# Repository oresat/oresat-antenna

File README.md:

# oresat-antenna
This is a place for RF details of the antennas used on the OreSat CubeSat

On the OreSat structure there are antennas placed on the +Z and -Z surfaces.

*  On the +Z surface is the directional helix antenna for high speed S-Band scientific communications. This is also known as
the _DxWiFi experiment_.

*  On the -Z surface is the tri-band omnidirectional (nearly "isotropic radiator") turnstile antenna used for:
   * UHF telemetry and engineering downlink
   * L-Band engineering uplink
   * A secondary S-Band up/downlink backup antenna

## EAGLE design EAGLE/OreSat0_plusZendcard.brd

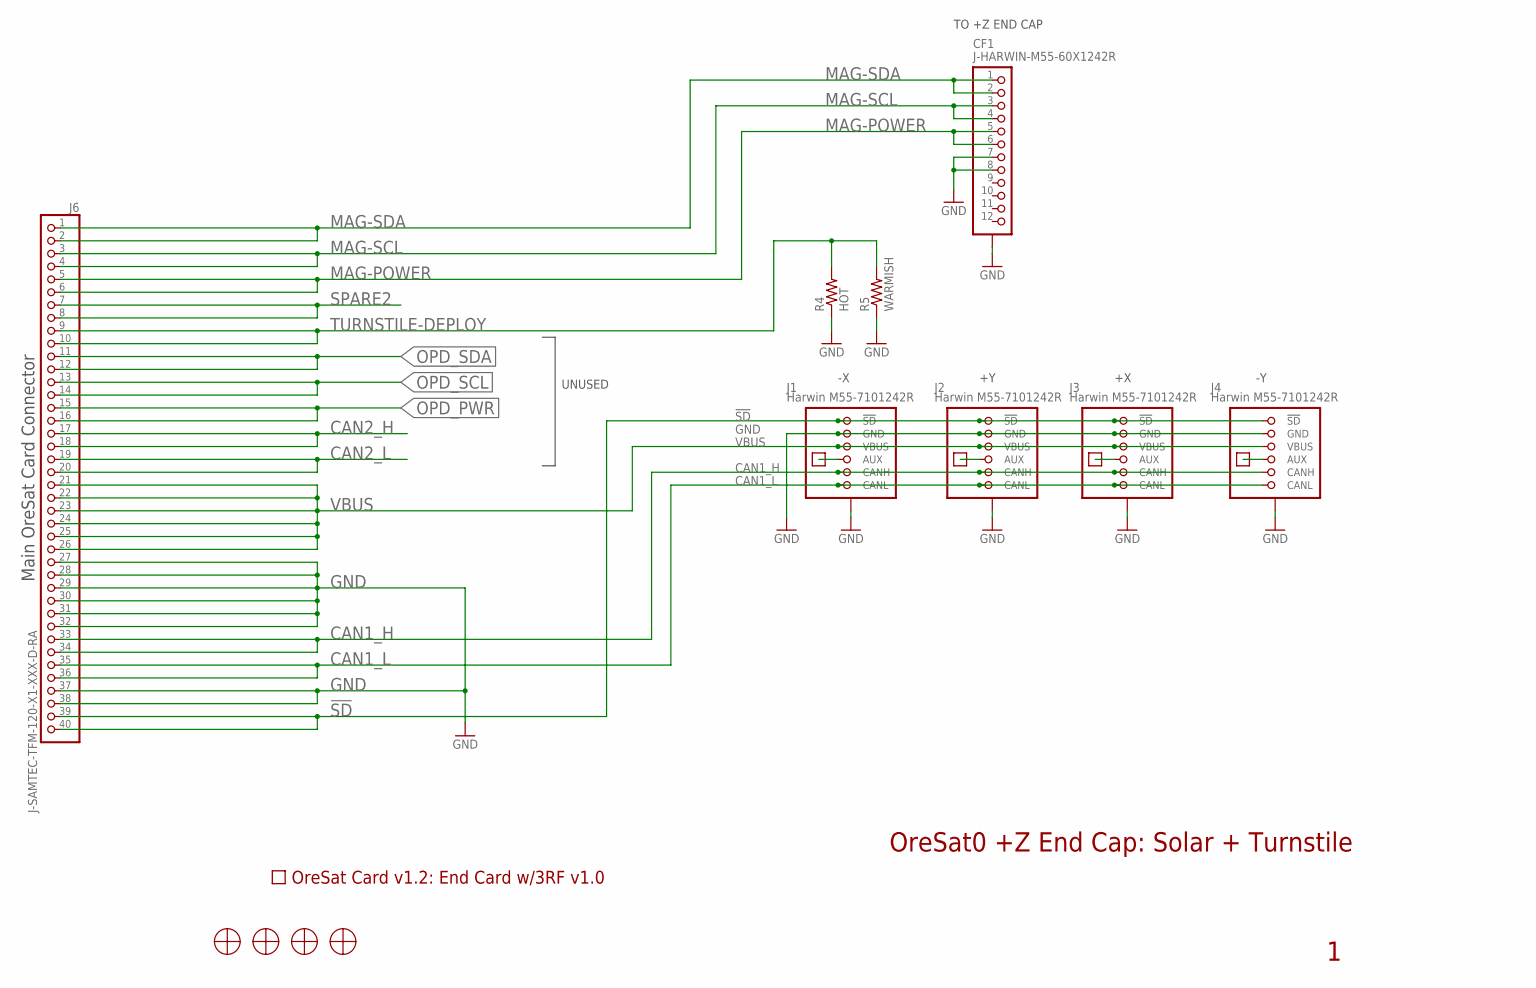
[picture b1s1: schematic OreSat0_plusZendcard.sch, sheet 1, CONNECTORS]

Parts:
CF1: J-HARWIN-M55-60X1242R; HARWIN-M55-60X1242R
J1, J2, J3, J4: Harwin M55-7101242R; M55-7101242R
J6: J-SAMTEC-TFM-120-X1-XXX-D-RA; MPN TFM-120-01-L-D-RA
PCB1: ORESAT-CARD-V1.3-END-CARD-3RF-V1.0
R4: HOT; 0309/12
R5: WARMISH; 0309/12
TP1, TP2, TP3, TP4: TEST-POINT-LARGE-SQUARE; 1X01
U$9, U$10, U$11, U$12: MCMASTER-94100A150

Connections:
!SD: J1.1 (!SD), J1.2 (!SD), J2.1 (!SD), J2.2 (!SD), J3.1 (!SD), J3.2 (!SD), J4.1 (!SD), J4.2 (!SD), J6.39, J6.40
CAN1_H: J1.9 (CANH), J1.10 (CANH), J2.9 (CANH), J2.10 (CANH), J3.9 (CANH), J3.10 (CANH), J4.9 (CANH), J4.10 (CANH), J6.33, J6.34
CAN1_L: J1.11 (CANL), J1.12 (CANL), J2.11 (CANL), J2.12 (CANL), J3.11 (CANL), J3.12 (CANL), J4.11 (CANL), J4.12 (CANL), J6.35, J6.36
CAN2_H: J6.17, J6.18
CAN2_L: J6.19, J6.20
GND: CF1.7, CF1.8, CF1.P$1 (SHIELDS), CF1.P$2 (SHIELDS), CF1.P$3 (SHIELDS), CF1.P$4 (SHIELDS), J1.3 (GND), J1.4 (GND), J1.P$1 (SHIELD), J1.P$2 (SHIELD), J1.P$3 (SHIELD), J1.P$4 (SHIELD), J2.3 (GND), J2.4 (GND), J2.P$1 (SHIELD), J2.P$2 (SHIELD), J2.P$3 (SHIELD), J2.P$4 (SHIELD), J3.3 (GND), J3.4 (GND), J3.P$1 (SHIELD), J3.P$2 (SHIELD), J3.P$3 (SHIELD), J3.P$4 (SHIELD), J4.3 (GND), J4.4 (GND), J4.P$1 (SHIELD), J4.P$2 (SHIELD), J4.P$3 (SHIELD), J4.P$4 (SHIELD), J6.27, J6.28, J6.29, J6.30, J6.31, J6.32, J6.37, J6.38, R4.1, R5.1; also elsewhere on the board
MAG-POWER: CF1.5, CF1.6, J6.5, J6.6
MAG-SCL: CF1.3, CF1.4, J6.3, J6.4
MAG-SDA: CF1.1, CF1.2, J6.1, J6.2
unnamed: J1.7 (AUX), J1.8 (AUX), TP1.1
unnamed: J2.7 (AUX), J2.8 (AUX), TP2.1
unnamed: J3.7 (AUX), J3.8 (AUX), TP3.1
unnamed: J4.7 (AUX), J4.8 (AUX), TP4.1
OPD_PWR: J6.15, J6.16
OPD_SCL: J6.13, J6.14
OPD_SDA: J6.11, J6.12
SPARE2: J6.7, J6.8
TURNSTILE-DEPLOY: J6.9, J6.10, R4.2, R5.2
VBUS: J1.5 (VBUS), J1.6 (VBUS), J2.5 (VBUS), J2.6 (VBUS), J3.5 (VBUS), J3.6 (VBUS), J4.5 (VBUS), J4.6 (VBUS), J6.21, J6.22, J6.23, J6.24, J6.25, J6.26

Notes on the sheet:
Main OreSat Card Connector
UNUSED
OreSat0 +Z End Cap: Solar + Turnstile
TO +Z END CAP

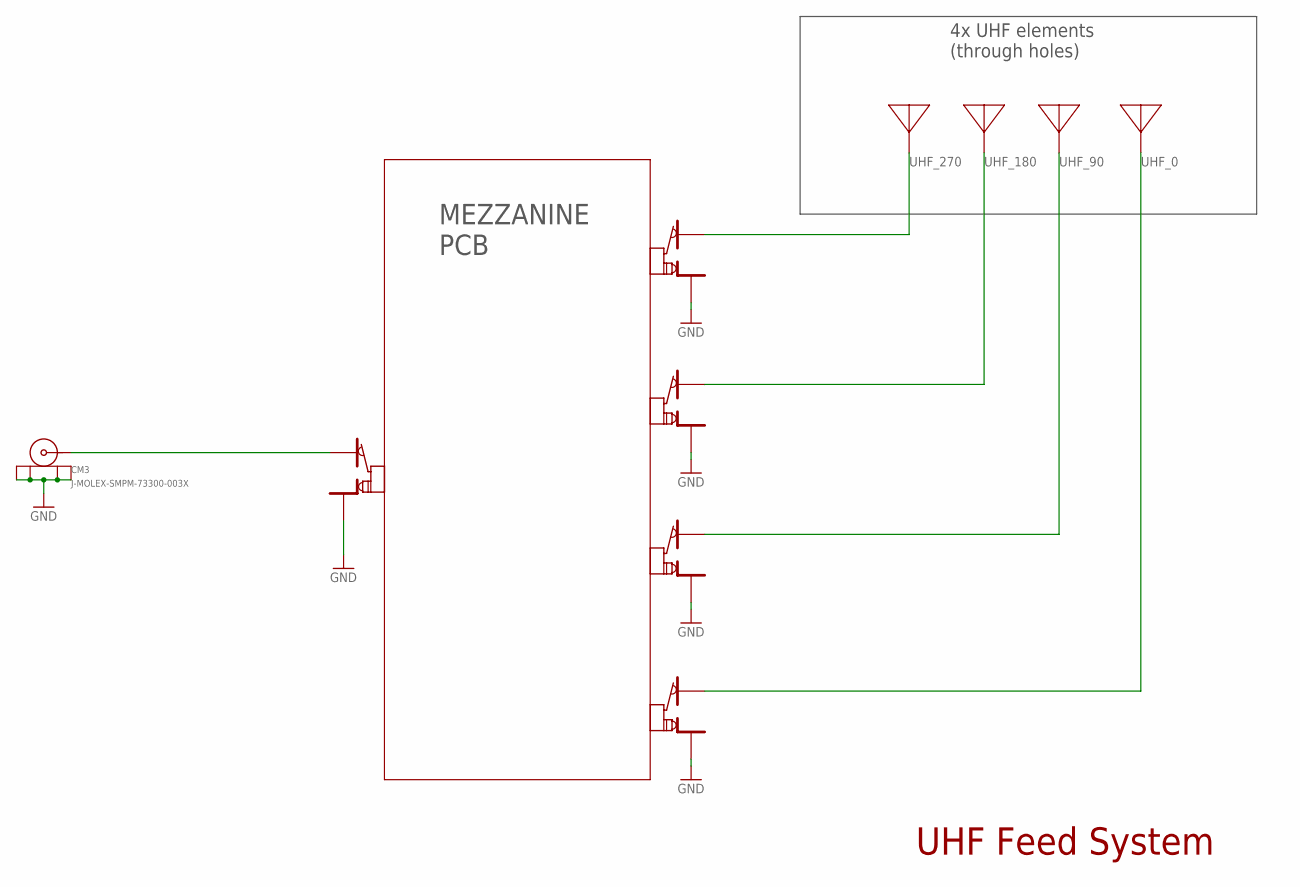
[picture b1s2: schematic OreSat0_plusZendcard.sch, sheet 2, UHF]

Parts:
CM3: J-MOLEX-SMPM-73300-003X
U$4, U$5, U$6, U$7, U$8: R107064070_CONTACT

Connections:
GND: CM3.P$1 (SHIELD3), CM3.P$2 (SHIELD2), CM3.P$3 (SHIELD1), CM3.P$4 (SHIELD), U$4.P$2, U$4.P$3, U$5.P$2, U$5.P$3, U$6.P$2, U$6.P$3, U$7.P$2, U$7.P$3, U$8.P$2, U$8.P$3; also elsewhere on the board
unnamed: CM3.RF (CENTER), U$4.P$1
UHF_0: U$8.P$1
UHF_90: U$7.P$1
UHF_180: U$6.P$1
UHF_270: U$5.P$1

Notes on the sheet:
MEZZANINE PCB
UHF Feed System
4x UHF elements (through holes)

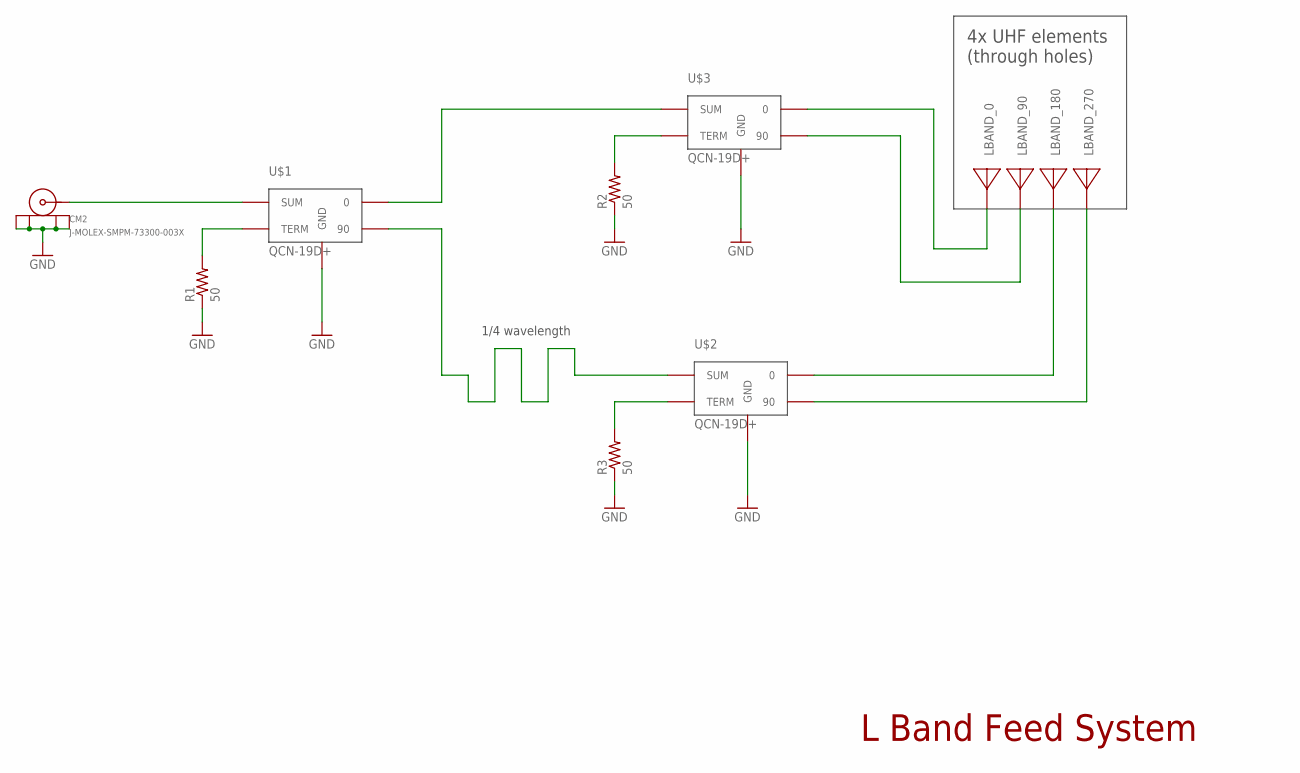
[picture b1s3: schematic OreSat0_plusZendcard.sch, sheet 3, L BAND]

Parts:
CM2: J-MOLEX-SMPM-73300-003X
R1, R2, R3: 50; .0805-B-NOSILK
U$1, U$2, U$3: QCN-19D+; QVN-19D+

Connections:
GND: CM2.P$1 (SHIELD3), CM2.P$2 (SHIELD2), CM2.P$3 (SHIELD1), CM2.P$4 (SHIELD), R1.1, R2.1, R3.1, U$1.P$2 (GND), U$1.P$5 (GND), U$2.P$2 (GND), U$2.P$5 (GND), U$3.P$2 (GND), U$3.P$5 (GND); also elsewhere on the board
LBAND_0: U$3.P$4 (0)
LBAND_90: U$3.P$6 (90)
LBAND_180: U$2.P$4 (0)
LBAND_270: U$2.P$6 (90)
unnamed: CM2.RF (CENTER), U$1.P$1 (SUM)
unnamed: U$1.P$4 (0), U$3.P$1 (SUM)
unnamed: R1.2, U$1.P$3 (TERM)
unnamed: R2.2, U$3.P$3 (TERM)
unnamed: U$1.P$6 (90), U$2.P$1 (SUM)
unnamed: R3.2, U$2.P$3 (TERM)

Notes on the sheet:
1/4 wavelength
L Band Feed System
4x UHF elements (through holes)

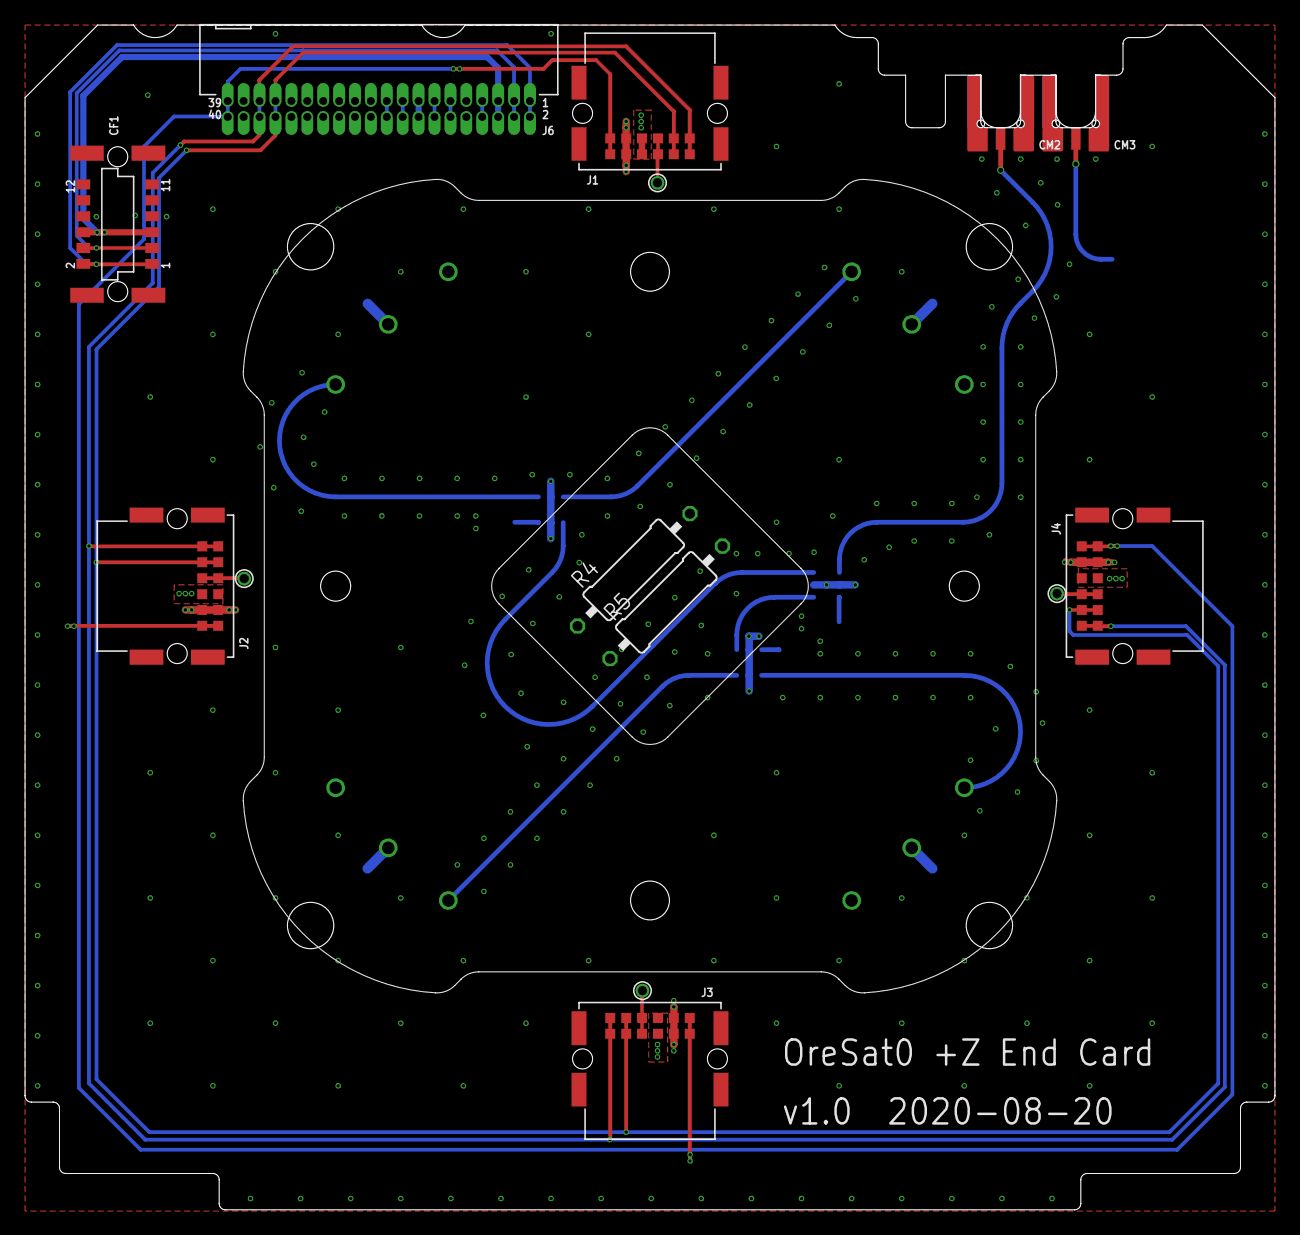
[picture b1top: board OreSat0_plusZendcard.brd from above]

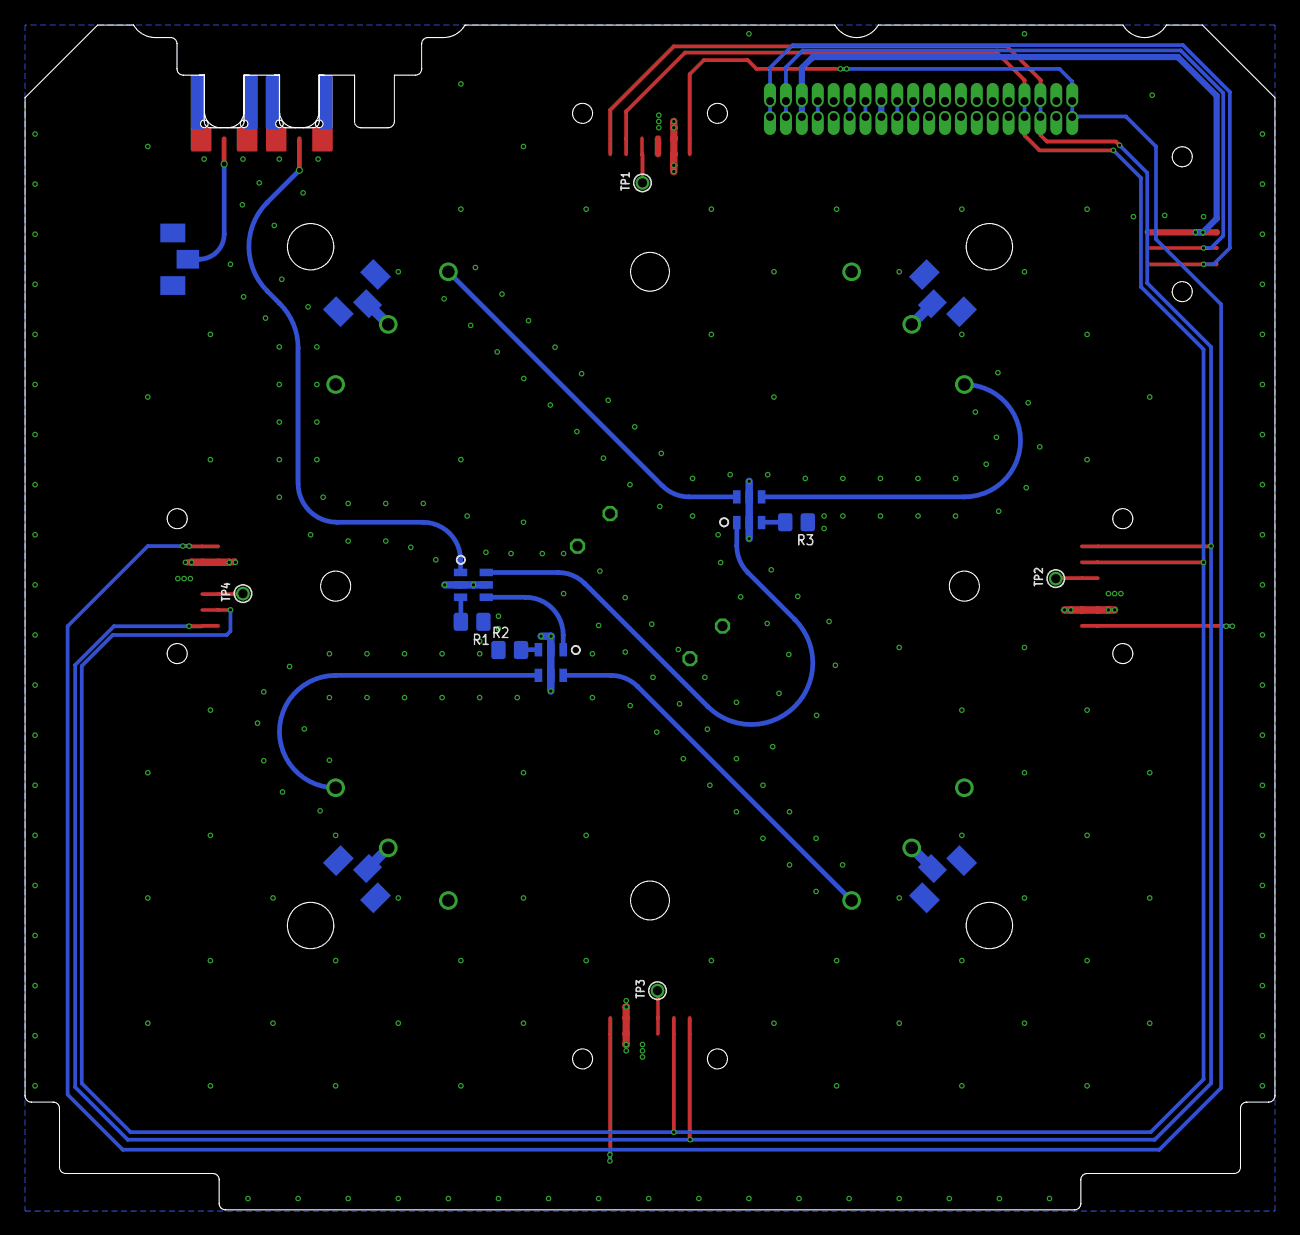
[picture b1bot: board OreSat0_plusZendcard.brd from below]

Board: 4 copper layers, 99.8 x 94.6 mm, 30 parts (11 on the bottom side), 26 nets.

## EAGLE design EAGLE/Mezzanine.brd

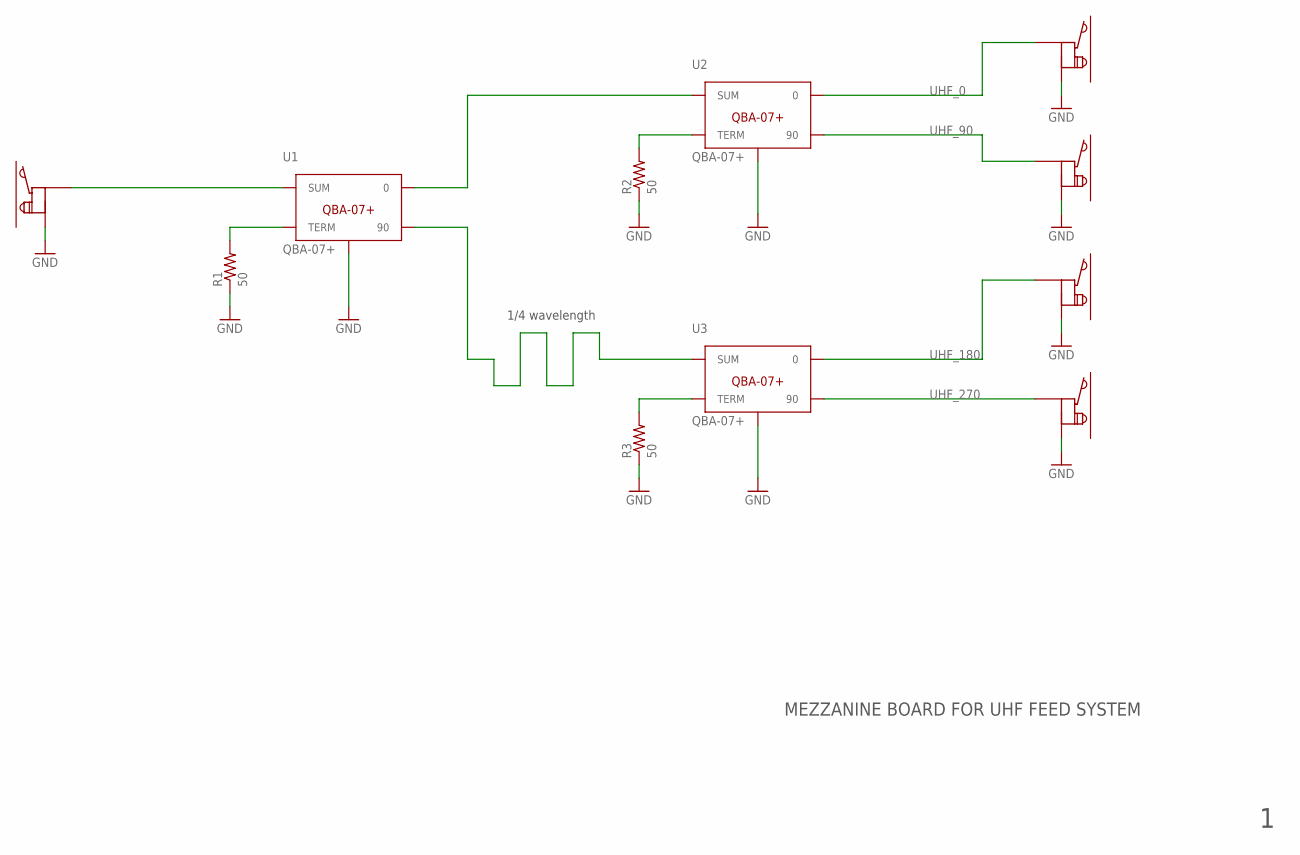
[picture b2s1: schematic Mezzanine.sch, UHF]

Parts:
R1, R2, R3: 50; .0805-B-NOSILK
U1, U2, U3: QBA-07+
U$1, U$2, U$3, U$4, U$5: R107064070

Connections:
GND: R1.1, R2.1, R3.1, U1.2 (GND), U1.3 (GND), U1.4 (GND), U1.7 (GND), U1.8 (GND), U1.9 (GND), U1.GND-NO-PAD (GND), U2.2 (GND), U2.3 (GND), U2.4 (GND), U2.7 (GND), U2.8 (GND), U2.9 (GND), U2.GND-NO-PAD (GND), U3.2 (GND), U3.3 (GND), U3.4 (GND), U3.7 (GND), U3.8 (GND), U3.9 (GND), U3.GND-NO-PAD (GND), U$1.P$2, U$1.P$3, U$2.P$2, U$2.P$3, U$3.P$2, U$3.P$3, U$4.P$2, U$4.P$3, U$5.P$2, U$5.P$3
unnamed: U1.1 (SUM), U$1.P$1
unnamed: U1.6 (0), U2.1 (SUM)
unnamed: R1.2, U1.5 (TERM)
unnamed: R2.2, U2.5 (TERM)
unnamed: U1.10 (90), U3.1 (SUM)
unnamed: R3.2, U3.5 (TERM)
UHF_0: U2.6 (0), U$2.P$1
UHF_90: U2.10 (90), U$3.P$1
UHF_180: U3.6 (0), U$4.P$1
UHF_270: U3.10 (90), U$5.P$1

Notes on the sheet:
1/4 wavelength
MEZZANINE BOARD FOR UHF FEED SYSTEM

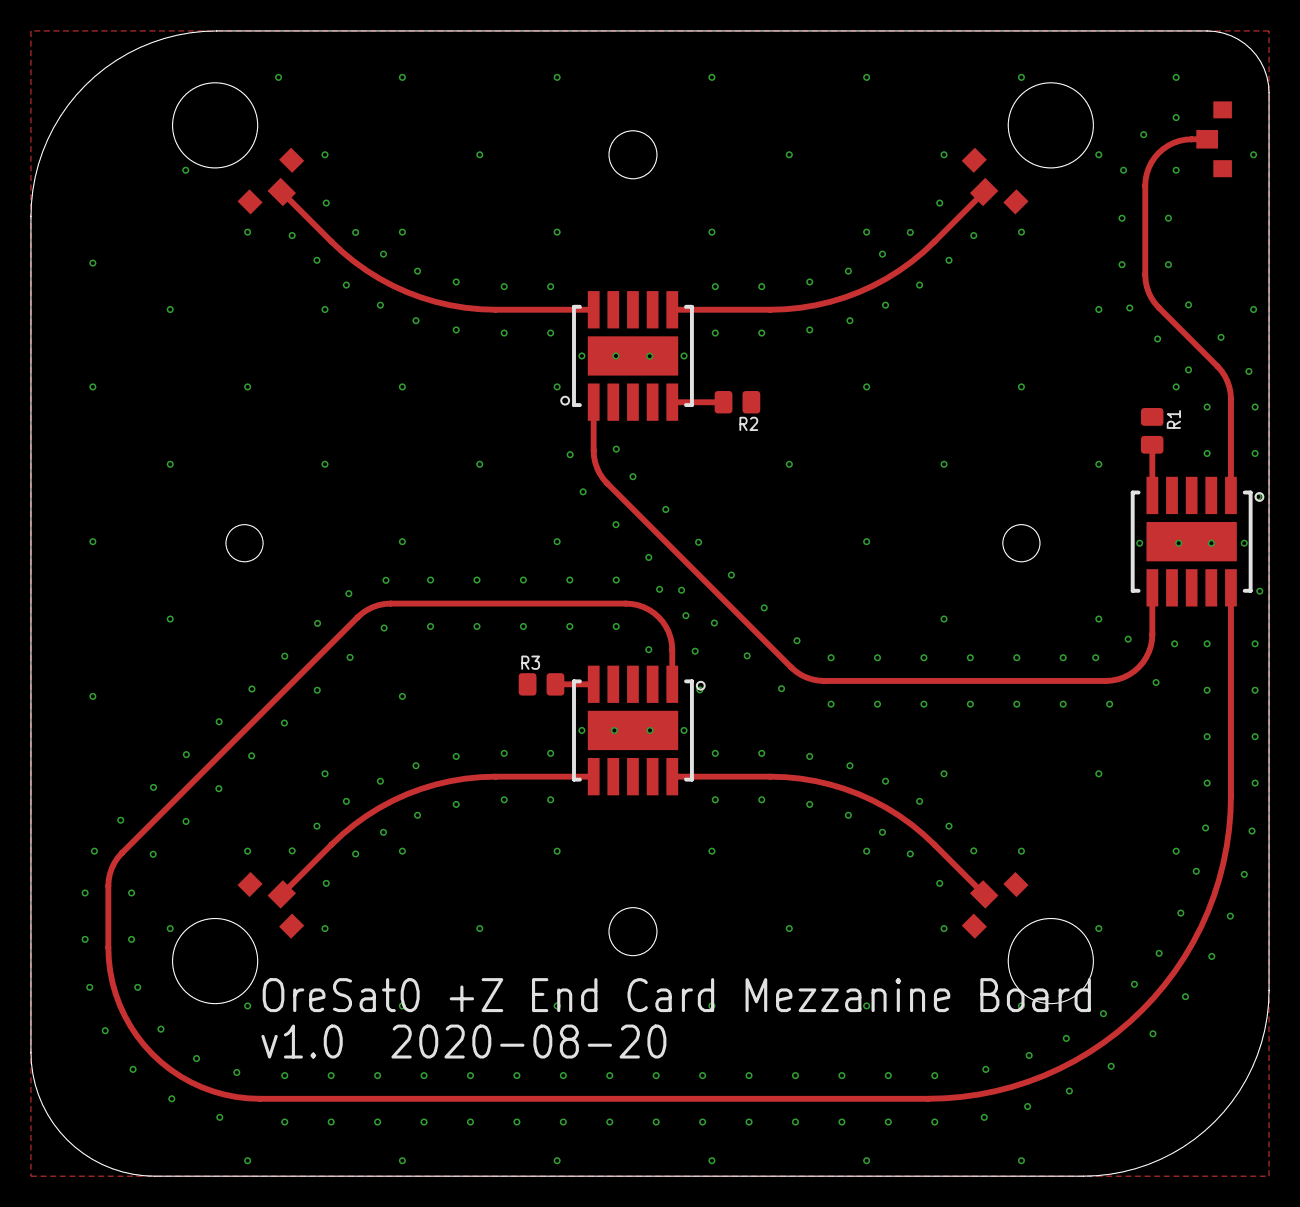
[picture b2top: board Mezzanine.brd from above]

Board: 4 copper layers, 80.0 x 74.0 mm, 11 parts (0 on the bottom side), 11 nets.

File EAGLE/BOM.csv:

Quantity,MFG,MFG_PN,DIST,DIST_PN,Generic
6,Vishay Dale,RCP0603W50R0GEB,Digi-Key,541-2655-1-ND,Y
1,Samtec Inc.,TFM-120-01-L-D-RA,Digi-Key,SAM10145-ND,N
4,Harwin Inc.,M55-7101242R,Digi-Key,952-3891-1-ND,N
1,Harwin Inc.,M55-6021242R,Digi-Key,952-3851-1-ND,N
5,Radiall,R107064070,Mouser,501-R107064070,N
3,Mini-Circuits,QCN-19+,Mouser,139-QCN-19,N
3,Mini-Circuits,QBA-07+,Mini-Circuits,QBA-07+,N
,,,,,
,,,,,
,,,,,
,,,,,
,,,,,

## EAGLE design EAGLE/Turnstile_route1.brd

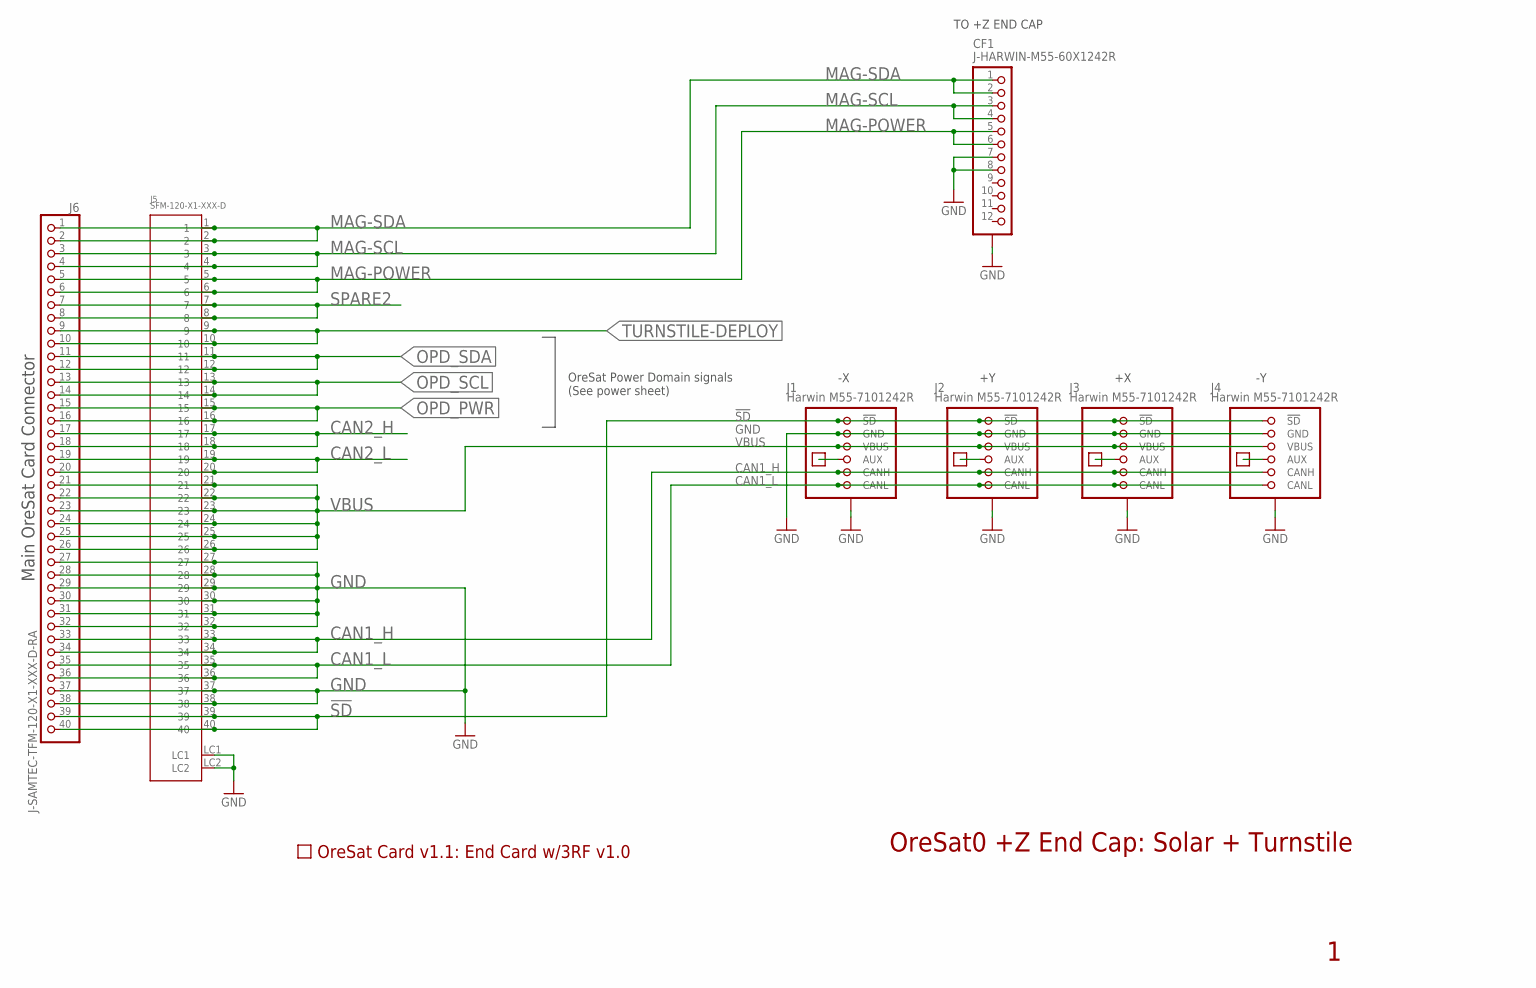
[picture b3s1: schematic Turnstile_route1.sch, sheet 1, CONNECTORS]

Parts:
CF1: J-HARWIN-M55-60X1242R; HARWIN-M55-60X1242R
J1, J2, J3, J4: Harwin M55-7101242R; M55-7101242R
J5: SFM-120-X1-XXX-D
J6: J-SAMTEC-TFM-120-X1-XXX-D-RA; MPN TFM-120-01-L-D-RA
PCB1: ORESAT-CARD-V1.1-END-CARD-3RF-V1.0; ORESAT-CARDV1.1-END-CARD-3RF-V1.0
TP1, TP2, TP3, TP4: TEST-POINT-LARGE-SQUARE; 1X01

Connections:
!SD: J1.1 (!SD), J1.2 (!SD), J2.1 (!SD), J2.2 (!SD), J3.1 (!SD), J3.2 (!SD), J4.1 (!SD), J4.2 (!SD), J5.39, J5.40, J6.39, J6.40
CAN1_H: J1.9 (CANH), J1.10 (CANH), J2.9 (CANH), J2.10 (CANH), J3.9 (CANH), J3.10 (CANH), J4.9 (CANH), J4.10 (CANH), J5.33, J5.34, J6.33, J6.34
CAN1_L: J1.11 (CANL), J1.12 (CANL), J2.11 (CANL), J2.12 (CANL), J3.11 (CANL), J3.12 (CANL), J4.11 (CANL), J4.12 (CANL), J5.35, J5.36, J6.35, J6.36
CAN2_H: J5.17, J5.18, J6.17, J6.18
CAN2_L: J5.19, J5.20, J6.19, J6.20
GND: CF1.7, CF1.8, CF1.P$1 (SHIELDS), CF1.P$2 (SHIELDS), CF1.P$3 (SHIELDS), CF1.P$4 (SHIELDS), J1.3 (GND), J1.4 (GND), J1.P$1 (SHIELD), J1.P$2 (SHIELD), J1.P$3 (SHIELD), J1.P$4 (SHIELD), J2.3 (GND), J2.4 (GND), J2.P$1 (SHIELD), J2.P$2 (SHIELD), J2.P$3 (SHIELD), J2.P$4 (SHIELD), J3.3 (GND), J3.4 (GND), J3.P$1 (SHIELD), J3.P$2 (SHIELD), J3.P$3 (SHIELD), J3.P$4 (SHIELD), J4.3 (GND), J4.4 (GND), J4.P$1 (SHIELD), J4.P$2 (SHIELD), J4.P$3 (SHIELD), J4.P$4 (SHIELD), J5.27, J5.28, J5.29, J5.30, J5.31, J5.32, J5.37, J5.38, J5.LC1, J5.LC2, J6.27, J6.28, J6.29, J6.30, J6.31, J6.32, J6.37, J6.38; also elsewhere on the board
MAG-POWER: CF1.5, CF1.6, J5.5, J5.6, J6.5, J6.6
MAG-SCL: CF1.3, CF1.4, J5.3, J5.4, J6.3, J6.4
MAG-SDA: CF1.1, CF1.2, J5.1, J5.2, J6.1, J6.2
unnamed: J1.7 (AUX), J1.8 (AUX), TP1.1
unnamed: J2.7 (AUX), J2.8 (AUX), TP2.1
unnamed: J3.7 (AUX), J3.8 (AUX), TP3.1
unnamed: J4.7 (AUX), J4.8 (AUX), TP4.1
OPD_PWR: J5.15, J5.16, J6.15, J6.16
OPD_SCL: J5.13, J5.14, J6.13, J6.14
OPD_SDA: J5.11, J5.12, J6.11, J6.12
SPARE2: J5.7, J5.8, J6.7, J6.8
TURNSTILE-DEPLOY: J5.9, J5.10, J6.9, J6.10
VBUS: J1.5 (VBUS), J1.6 (VBUS), J2.5 (VBUS), J2.6 (VBUS), J3.5 (VBUS), J3.6 (VBUS), J4.5 (VBUS), J4.6 (VBUS), J5.21, J5.22, J5.23, J5.24, J5.25, J5.26, J6.21, J6.22, J6.23, J6.24, J6.25, J6.26

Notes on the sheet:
Main OreSat Card Connector
OreSat Power Domain signals (See power sheet)
OreSat0 +Z End Cap: Solar + Turnstile
TO +Z END CAP

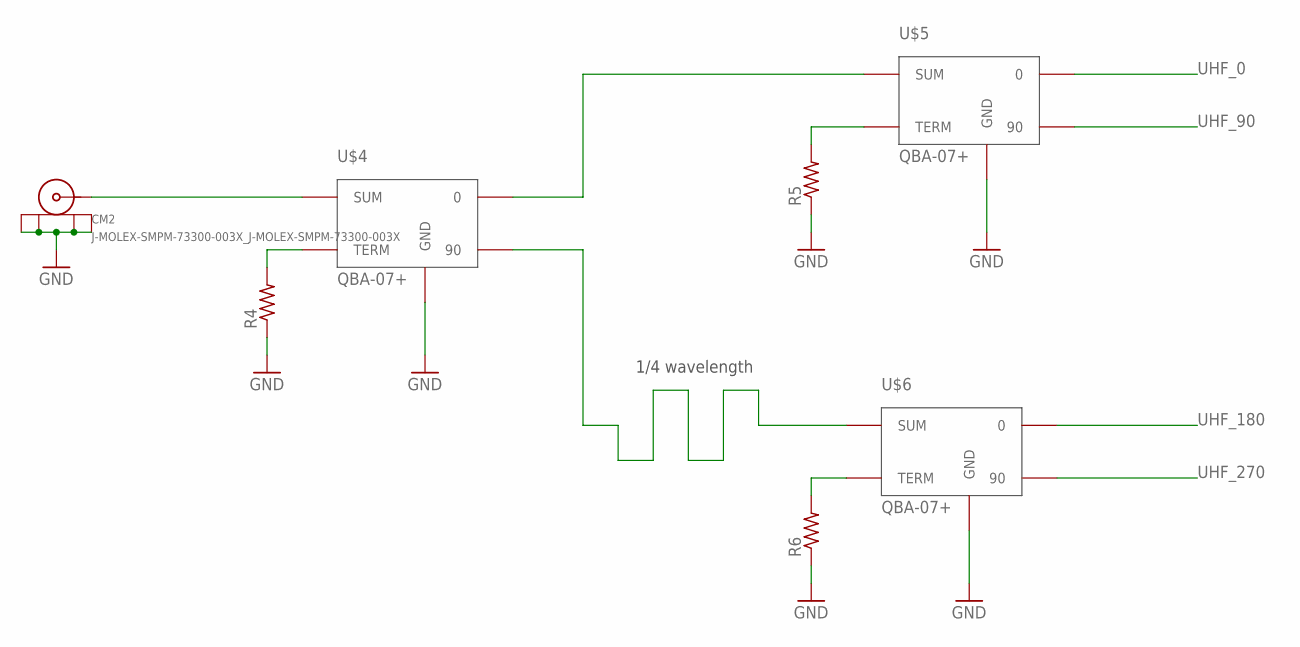
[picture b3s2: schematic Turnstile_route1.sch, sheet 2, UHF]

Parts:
CM2: J-MOLEX-SMPM-73300-003X_J-MOLEX-SMPM-73300-003X; J-MOLEX-SMPM-73300-003X_J-MOLEX-SMPM-073300-003X
R4, R5, R6: R-US_0402-A-NOSILK; .0402-A-NOSILK
U$4, U$5, U$6: QBA-07+

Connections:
GND: CM2.P$1 (SHIELD3), CM2.P$2 (SHIELD2), CM2.P$3 (SHIELD1), CM2.P$4 (SHIELD), R4.1, R5.1, R6.1, U$4.P$2 (GND), U$4.P$3 (GND), U$4.P$4 (GND), U$4.P$7 (GND), U$4.P$8 (GND), U$4.P$9 (GND), U$4.P$11 (GND), U$5.P$2 (GND), U$5.P$3 (GND), U$5.P$4 (GND), U$5.P$7 (GND), U$5.P$8 (GND), U$5.P$9 (GND), U$5.P$11 (GND), U$6.P$2 (GND), U$6.P$3 (GND), U$6.P$4 (GND), U$6.P$7 (GND), U$6.P$8 (GND), U$6.P$9 (GND), U$6.P$11 (GND); also elsewhere on the board
unnamed: CM2.RF (CENTER), U$4.P$1 (SUM)
unnamed: U$4.P$6 (0), U$5.P$1 (SUM)
unnamed: R4.2, U$4.P$5 (TERM)
unnamed: R5.2, U$5.P$5 (TERM)
unnamed: U$4.P$10 (90), U$6.P$1 (SUM)
unnamed: R6.2, U$6.P$5 (TERM)
UHF_0: U$5.P$6 (0)
UHF_90: U$5.P$10 (90)
UHF_180: U$6.P$6 (0)
UHF_270: U$6.P$10 (90)

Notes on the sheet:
1/4 wavelength

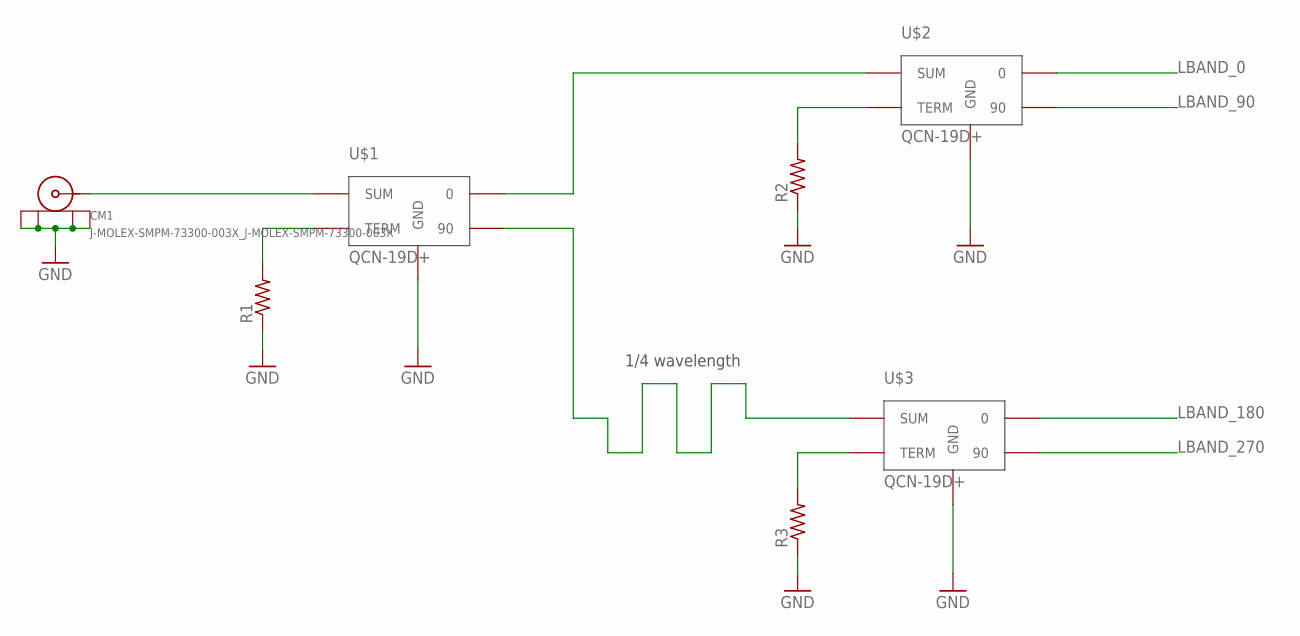
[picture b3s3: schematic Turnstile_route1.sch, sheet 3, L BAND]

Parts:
CM1: J-MOLEX-SMPM-73300-003X_J-MOLEX-SMPM-73300-003X; J-MOLEX-SMPM-73300-003X_J-MOLEX-SMPM-073300-003X
R1, R2, R3: R-US_0402-A-NOSILK; .0402-A-NOSILK
U$1, U$2, U$3: QCN-19D+; QVN-19D+

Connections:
GND: CM1.P$1 (SHIELD3), CM1.P$2 (SHIELD2), CM1.P$3 (SHIELD1), CM1.P$4 (SHIELD), R1.1, R2.1, R3.1, U$1.P$2 (GND), U$1.P$5 (GND), U$2.P$2 (GND), U$2.P$5 (GND), U$3.P$2 (GND), U$3.P$5 (GND); also elsewhere on the board
LBAND_0: U$2.P$4 (0)
LBAND_90: U$2.P$6 (90)
LBAND_180: U$3.P$4 (0)
LBAND_270: U$3.P$6 (90)
unnamed: CM1.RF (CENTER), U$1.P$1 (SUM)
unnamed: U$1.P$4 (0), U$2.P$1 (SUM)
unnamed: R1.2, U$1.P$3 (TERM)
unnamed: R2.2, U$2.P$3 (TERM)
unnamed: U$1.P$6 (90), U$3.P$1 (SUM)
unnamed: R3.2, U$3.P$3 (TERM)

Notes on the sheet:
1/4 wavelength

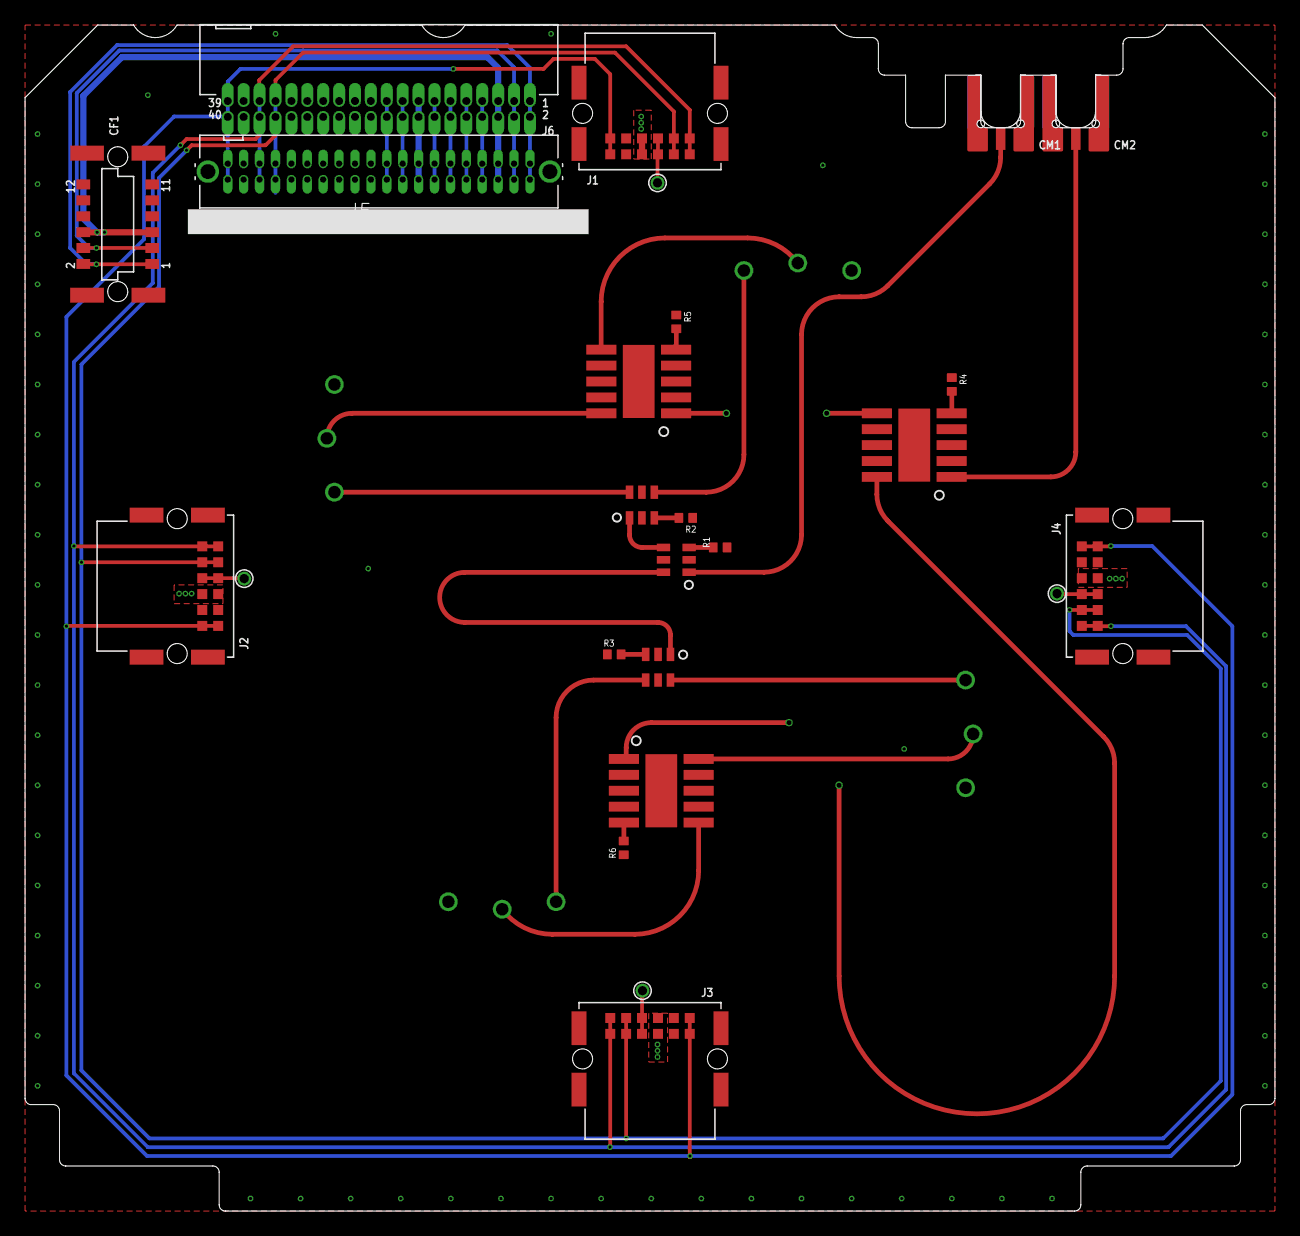
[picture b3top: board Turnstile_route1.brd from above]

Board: 4 copper layers, 99.8 x 94.7 mm, 26 parts (0 on the bottom side), 31 nets.

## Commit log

2017-09-09 Add turnstile design document and prototype testing information
2019-04-25 Update README with latest antenna info
2019-06-19 Initial release into github of helical components.
    TODO:
    Re-model of helical arm/base for DFM
    Increase size of hinges
    Adjust size to correct helical dimensions (Andrew knows which)
2019-08-20 "auto-generated from update_repos.py"
2020-07-07 Helix Simulations
2020-07-08 mechanical specs for the helical
2020-07-08 Mech Sim update
2020-07-10 turnstile base models
2020-07-10 Turnstile basic structure and Simulations prepared
2020-07-10 simulation results
2020-07-23 Turnstile stuff
2020-07-24 OMG, there's a lot on thie board! Added main connector, solar connectors, end cap connector, and new and improved debug connector which is the best thing ever. Good luck Eric!
2020-07-30 turnstile Route
2020-08-17 Rough draft
2020-08-18 rough layout with mezzanine
2020-08-18 Corrected Rough draft
2020-08-18 error checks done
2020-08-19 TestBoard ready for design review and order
2020-08-19 File Clean up
2020-08-20 SHIP IT
2020-08-20 error correction
2020-08-20 Design review cleanup of Eric's perfectly decent board. Added RF class, moved burnwires for maximum OCD placement, cleaned up schematic a little bit.
2020-08-21 rerouted mezzanine
2020-08-21 Minor additions to Eric's lovely boards: Made SD more robust (double vias) with larger isolate, added thicker traces and vias to solar grounds, and chose actual fasteners for the mezzanine board, whi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
2020-08-21 Minor additions to Eric's board: Brought in edges to make it slightly smaller because money and it doesn't need to be big, and added appropriate fasteners, including shoulder bolts in the X axis for 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
2020-08-21 Yikes! Forgot name and version.
2020-08-25 Updated QBA footprints to have no solder mask in order to generate the correct solder paste stencils.
2020-08-25 Updated some parts to have attributes assigned
2020-09-07 bom update
2020-09-10 Actual BOM for the OreSat0 +Z End Card with mezzanine board
2020-09-22 ansys model updates
2020-10-27 Update mezzanine board to slide in past nubs
2020-10-31 quarter wave transform simulation for 2.422GHz
2020-11-23 +Z end card new outline and fasteners
2020-11-23 Moved OreSat0 +Z end card to the oresat-end-card repo, where it really ought to be.
